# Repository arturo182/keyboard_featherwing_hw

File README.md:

# The Keyboard FeatherWing

The Keyboard FeatherWing is an easy way to add a handheld Qwerty keyboard and a 2.6 color display (+ more) to your project! It fits well in your hands and is great for typing with your thumbs, early 2000s-style.

The FeatherWing itself does not contain an MCU/CPU/SoC that you can program; you will need a board compatible with the [Adafruit Feather System](https://learn.adafruit.com/adafruit-feather/feather-specification).

# Technical details
- 2.6 320x240 16-bit color LCD with resistive touch screen
- QWERTY keyboard
- 5-way button
- 4 soft tactile buttons
- A Neopixel
- microSD connector
- Stemma QT/Qwiic connector
- On/Off switch
- Dual row sockets
- Four mounting holes
- GPIO solder jumpers

# Links

For more information visit https://kfw.solder.party/

You can find example code here: https://github.com/arturo182/keyboard_featherwing_sw

This board uses a ATSAMD20 chip as a i2c peripheral that can be polled to get the key FIFO, the firmware for the SAM can be found here: https://github.com/arturo182/bbq10kbd_i2c_sw

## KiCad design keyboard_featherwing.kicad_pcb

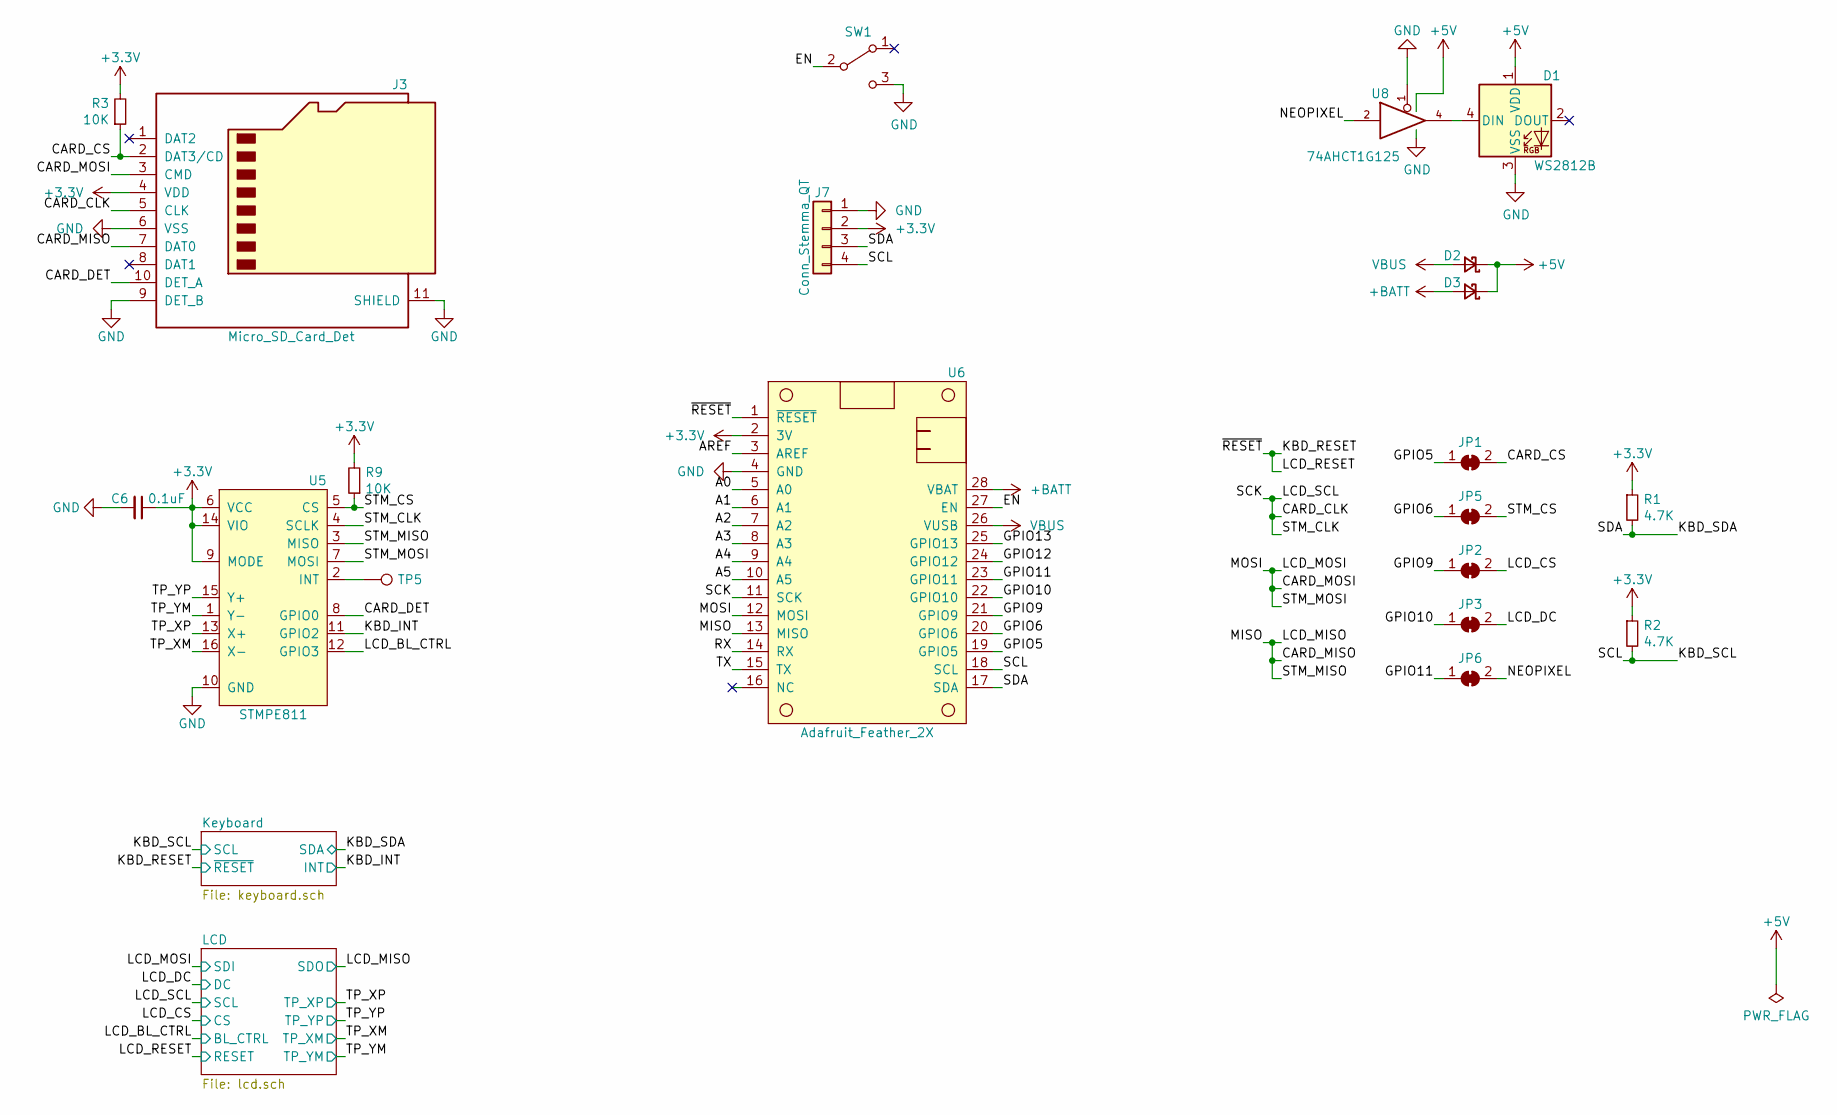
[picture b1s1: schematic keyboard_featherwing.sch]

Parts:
C6: 0.1uF; C_0603_1608Metric
D1: WS2812B; LED_WS2812B_PLCC4_5.0x5.0mm_P3.2mm
D2, D3: S1JHE; D_SOD-323_HandSoldering
J3: Micro_SD_Card_Det; microSD_HC_Molex_104031-0811
J7: Conn_Stemma_QT; JST_SH_SM04B-SRSS-TB_1x04-1MP_P1.00mm_Horizontal
JP1: SB_CARD_CS; SolderJumper-2_P1.3mm_Bridged_RoundedPad1.0x1.5mm
JP2: SB_LCD_CS; SolderJumper-2_P1.3mm_Bridged_RoundedPad1.0x1.5mm
JP3: SB_LCD_DC; SolderJumper-2_P1.3mm_Bridged_RoundedPad1.0x1.5mm
JP5: SB_STM_CS; SolderJumper-2_P1.3mm_Bridged_RoundedPad1.0x1.5mm
JP6: SB_NEOPIXEL; SolderJumper-2_P1.3mm_Bridged_RoundedPad1.0x1.5mm
R1, R2: 4.7K; R_0603_1608Metric
R3, R9: 10K; R_0603_1608Metric
SW1: SW_EN; SW_SPDT_PCM12
TP5: TP_STM_INT; TestPoint_Pad_D3.0mm
U5: STMPE811; QFN-16-1EP_3x3mm_P0.5mm_EP1.75x1.75mm
U6: Adafruit_Feather_2X; FeatherWing
U8: 74AHCT1G125; SOT-353_SC-70-5

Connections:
+3V3: C6.1, J3.4 (VDD), J7.2, R1.1, R2.1, R3.2, R9.2, U5.6 (VCC), U5.9 (MODE), U5.14 (VIO), U6.2 (3V); also elsewhere on the board
+5V: D1.1 (VDD), D2.1 (K), D3.1 (K), U8.5 (VCC)
+BATT: D3.2 (A), U6.28 (VBAT)
/A0: U6.5 (A0)
/A1: U6.6 (A1)
/A2: U6.7 (A2)
/A3: U6.8 (A3)
/A4: U6.9 (A4)
/A5: U6.10 (A5)
/AREF: U6.3 (AREF)
/CARD_CLK: J3.5 (CLK), U5.4 (SCLK), U6.11 (SCK); also elsewhere on the board
/CARD_CS: J3.2 (DAT3/CD), JP1.2 (B), R3.1
/CARD_DET: J3.10 (DET_A), U5.8 (GPIO0)
/CARD_MISO: J3.7 (DAT0), U5.3 (MISO), U6.13 (MISO); also elsewhere on the board
/CARD_MOSI: J3.3 (CMD), U5.7 (MOSI), U6.12 (MOSI); also elsewhere on the board
/EN: SW1.2 (B), U6.27 (EN)
/GPIO5: JP1.1 (A), U6.19 (GPIO5)
/GPIO6: JP5.1 (A), U6.20 (GPIO6)
/GPIO9: JP2.1 (A), U6.21 (GPIO9)
/GPIO10: JP3.1 (A), U6.22 (GPIO10)
/GPIO11: JP6.1 (A), U6.23 (GPIO11)
/GPIO12: U6.24 (GPIO12)
/GPIO13: U6.25 (GPIO13)
/KBD_INT: U5.11 (GPIO2); also elsewhere on the board
/KBD_RESET: U6.1 (~RESET~); also elsewhere on the board
/KBD_SCL: J7.4, R2.2, U6.18 (SCL); also elsewhere on the board
/KBD_SDA: J7.3, R1.2, U6.17 (SDA); also elsewhere on the board
/LCD_BL_CTRL: U5.12 (GPIO3); also elsewhere on the board
/LCD_CS: JP2.2 (B); also elsewhere on the board
/LCD_DC: JP3.2 (B); also elsewhere on the board
/NEOPIXEL: JP6.2 (B), U8.2
/RX: U6.14 (RX)
/STM_CS: JP5.2 (B), R9.1, U5.5 (CS)
/TP_XM: U5.16 (X-); also elsewhere on the board
/TP_XP: U5.13 (X+); also elsewhere on the board
/TP_YM: U5.1 (Y-); also elsewhere on the board
/TP_YP: U5.15 (Y+); also elsewhere on the board
/TX: U6.15 (TX)
GND: C6.2, D1.3 (VSS), J3.6 (VSS), J3.9 (DET_B), J3.11 (SHIELD), J7.1, SW1.3 (C), U5.10 (GND), U6.4 (GND), U8.1, U8.3 (GND); also elsewhere on the board
unnamed: D1.4 (DIN), U8.4
unnamed: TP5.1, U5.2 (INT)
VBUS: D2.2 (A), U6.26 (VUSB)

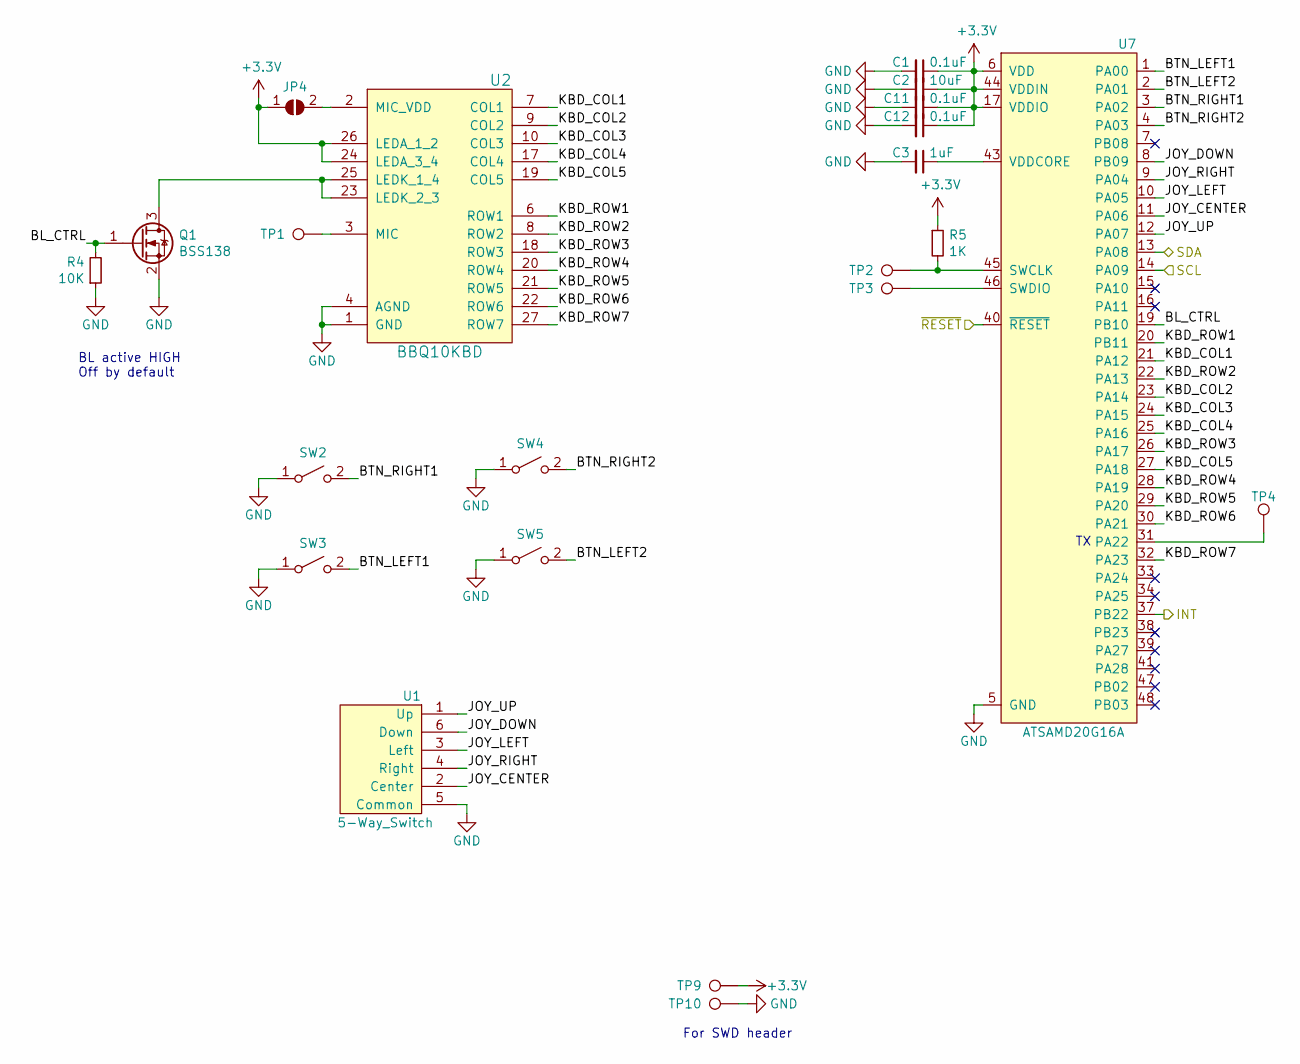
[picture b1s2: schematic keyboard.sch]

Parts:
C1, C11, C12: 0.1uF; C_0603_1608Metric
C2: 10uF; C_0603_1608Metric
C3: 1uF; C_0603_1608Metric
JP4: SB_MIC_VDD; SolderJumper-2_P1.3mm_Open_RoundedPad1.0x1.5mm
Q1: BSS138; SOT-23
R4: 10K; R_0603_1608Metric
R5: 1K; R_0603_1608Metric
SW2: SW_RIGHT1; RMT-CZ66
SW3: SW_LEFT1; RMT-CZ66
SW4: SW_RIGHT2; RMT-CZ66
SW5: SW_LEFT2; RMT-CZ66
TP1: TP_MIC; TestPoint_Pad_D3.0mm
TP2: TP_KBD_SWCLK; TestPoint_Pad_D3.0mm
TP3: TP_KBD_SWDIO; TestPoint_Pad_D3.0mm
TP4: TP_KBD_TX; TestPoint_Pad_D3.0mm
TP9: TP_KBD_3V; TestPoint_Pad_D3.0mm
TP10: TP_KBD_GND; TestPoint_Pad_D3.0mm
U1: 5-Way_Switch; SF303GJ26
U2: BBQ10KBD; BM14B(0.8)-24DS-0.4V(53)
U7: ATSAMD20G16A; QFN-48-1EP_7x7mm_P0.5mm_EP5.15x5.15mm

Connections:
+3V3: C1.1, C2.1, C11.1, C12.1, JP4.1 (A), R5.1, TP9.1, U2.24 (LEDA_3_4), U2.26 (LEDA_1_2), U7.6 (VDD), U7.17 (VDDIO), U7.36 (VDDIO), U7.44 (VDDIN); also elsewhere on the board
/KBD_INT: U7.37 (PB22); also elsewhere on the board
/KBD_RESET: U7.40 (~RESET~); also elsewhere on the board
/KBD_SCL: U7.14 (PA09); also elsewhere on the board
/KBD_SDA: U7.13 (PA08); also elsewhere on the board
/Keyboard/BL_CTRL: Q1.1 (G), R4.2, U7.19 (PB10)
/Keyboard/BTN_LEFT1: SW3.2 (B), U7.1 (PA00)
/Keyboard/BTN_LEFT2: SW5.2 (B), U7.2 (PA01)
/Keyboard/BTN_RIGHT1: SW2.2 (B), U7.3 (PA02)
/Keyboard/BTN_RIGHT2: SW4.2 (B), U7.4 (PA03)
/Keyboard/JOY_CENTER: U1.2 (Center), U7.11 (PA06)
/Keyboard/JOY_DOWN: U1.6 (Down), U7.8 (PB09)
/Keyboard/JOY_LEFT: U1.3 (Left), U7.10 (PA05)
/Keyboard/JOY_RIGHT: U1.4 (Right), U7.9 (PA04)
/Keyboard/JOY_UP: U1.1 (Up), U7.12 (PA07)
/Keyboard/KBD_COL1: U2.7 (COL1), U7.21 (PA12)
/Keyboard/KBD_COL2: U2.9 (COL2), U7.23 (PA14)
/Keyboard/KBD_COL3: U2.10 (COL3), U7.24 (PA15)
/Keyboard/KBD_COL4: U2.17 (COL4), U7.25 (PA16)
/Keyboard/KBD_COL5: U2.19 (COL5), U7.27 (PA18)
/Keyboard/KBD_ROW1: U2.6 (ROW1), U7.20 (PB11)
/Keyboard/KBD_ROW2: U2.8 (ROW2), U7.22 (PA13)
/Keyboard/KBD_ROW3: U2.18 (ROW3), U7.26 (PA17)
/Keyboard/KBD_ROW4: U2.20 (ROW4), U7.28 (PA19)
/Keyboard/KBD_ROW5: U2.21 (ROW5), U7.29 (PA20)
/Keyboard/KBD_ROW6: U2.22 (ROW6), U7.30 (PA21)
/Keyboard/KBD_ROW7: U2.27 (ROW7), U7.32 (PA23)
GND: C1.2, C2.2, C3.2, C11.2, C12.2, Q1.2 (S), R4.1, SW2.1 (A), SW3.1 (A), SW4.1 (A), SW5.1 (A), TP10.1, U1.5 (Common), U1.SHIELD, U2.1 (GND), U2.4 (AGND), U2.5 (GND), U2.11 (GND), U2.12 (GND), U2.13 (GND), U2.14 (GND), U2.15 (GND), U2.16 (GND), U2.28 (GND), U7.5 (GND), U7.18 (GND), U7.35 (GND), U7.42 (GND); also elsewhere on the board
unnamed: C3.1, U7.43 (VDDCORE)
unnamed: JP4.2 (B), U2.2 (MIC_VDD)
unnamed: Q1.3 (D), U2.23 (LEDK_2_3), U2.25 (LEDK_1_4)
unnamed: R5.2, TP2.1, U7.45 (SWCLK)
unnamed: TP1.1, U2.3 (MIC)
unnamed: TP3.1, U7.46 (SWDIO)
unnamed: TP4.1, U7.31 (PA22)

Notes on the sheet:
BL active HIGH Off by default
For SWD header

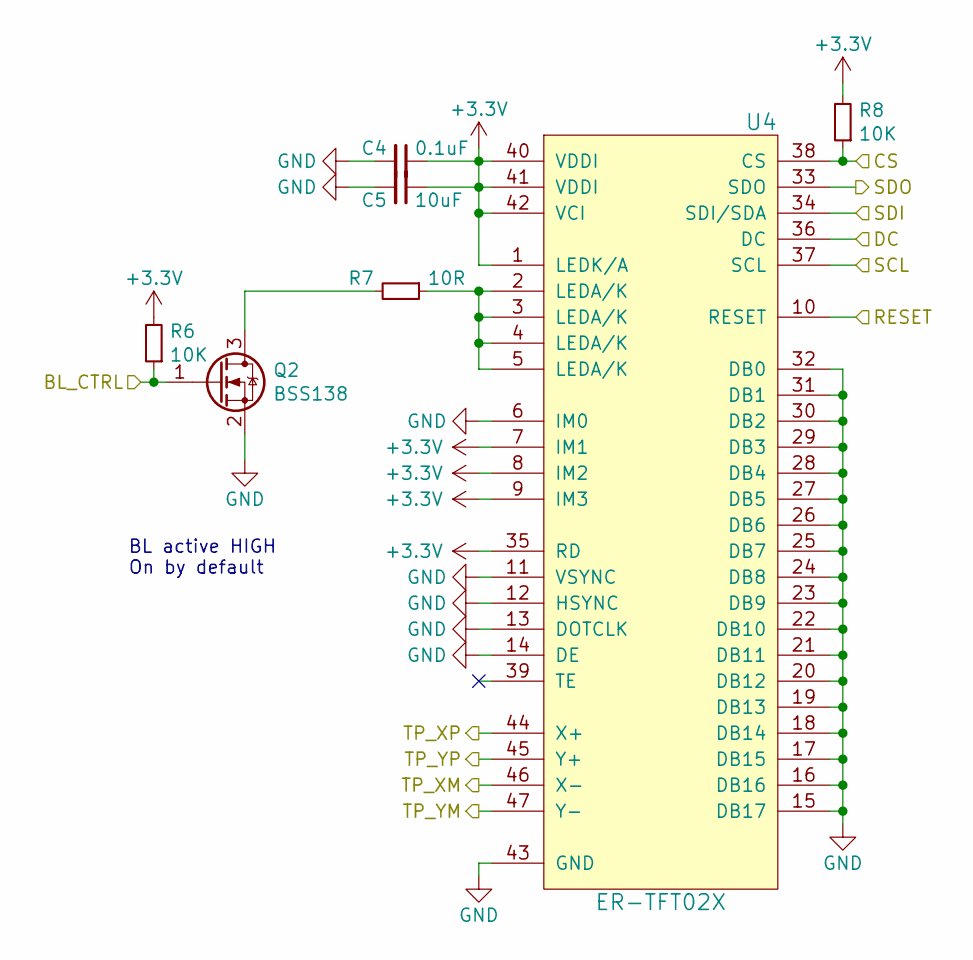
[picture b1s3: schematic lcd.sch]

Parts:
C4: 0.1uF; C_0603_1608Metric
C5: 10uF; C_0603_1608Metric
Q2: BSS138; SOT-23
R6, R8: 10K; R_0603_1608Metric
R7: 10R; R_0603_1608Metric
U4: ER-TFT02X; ER-CON50HT-1

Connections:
+3V3: C4.1, C5.1, R6.2, R8.2, U4.1 (LEDK/A), U4.7 (IM1), U4.8 (IM2), U4.9 (IM3), U4.35 (RD), U4.40 (VDDI), U4.41 (VDDI), U4.42 (VCI); also elsewhere on the board
/CARD_CLK: U4.37 (SCL); also elsewhere on the board
/CARD_MISO: U4.33 (SDO); also elsewhere on the board
/CARD_MOSI: U4.34 (SDI/SDA); also elsewhere on the board
/KBD_RESET: U4.10 (RESET); also elsewhere on the board
/LCD_BL_CTRL: Q2.1 (G), R6.1; also elsewhere on the board
/LCD_CS: R8.1, U4.38 (CS); also elsewhere on the board
/LCD_DC: U4.36 (DC); also elsewhere on the board
/TP_XM: U4.46 (X-); also elsewhere on the board
/TP_XP: U4.44 (X+); also elsewhere on the board
/TP_YM: U4.47 (Y-); also elsewhere on the board
/TP_YP: U4.45 (Y+); also elsewhere on the board
GND: C4.2, C5.2, Q2.2 (S), U4.6 (IM0), U4.11 (VSYNC), U4.12 (HSYNC), U4.13 (DOTCLK), U4.14 (DE), U4.15 (DB17), U4.16 (DB16), U4.17 (DB15), U4.18 (DB14), U4.19 (DB13), U4.20 (DB12), U4.21 (DB11), U4.22 (DB10), U4.23 (DB9), U4.24 (DB8), U4.25 (DB7), U4.26 (DB6), U4.27 (DB5), U4.28 (DB4), U4.29 (DB3), U4.30 (DB2), U4.31 (DB1), U4.32 (DB0), U4.43 (GND), U4.48 (GND), U4.49 (GND), U4.50 (GND); also elsewhere on the board
unnamed: Q2.3 (D), R7.2
unnamed: R7.1, U4.2 (LEDA/K), U4.3 (LEDA/K), U4.4 (LEDA/K), U4.5 (LEDA/K)

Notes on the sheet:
BL active HIGH On by default

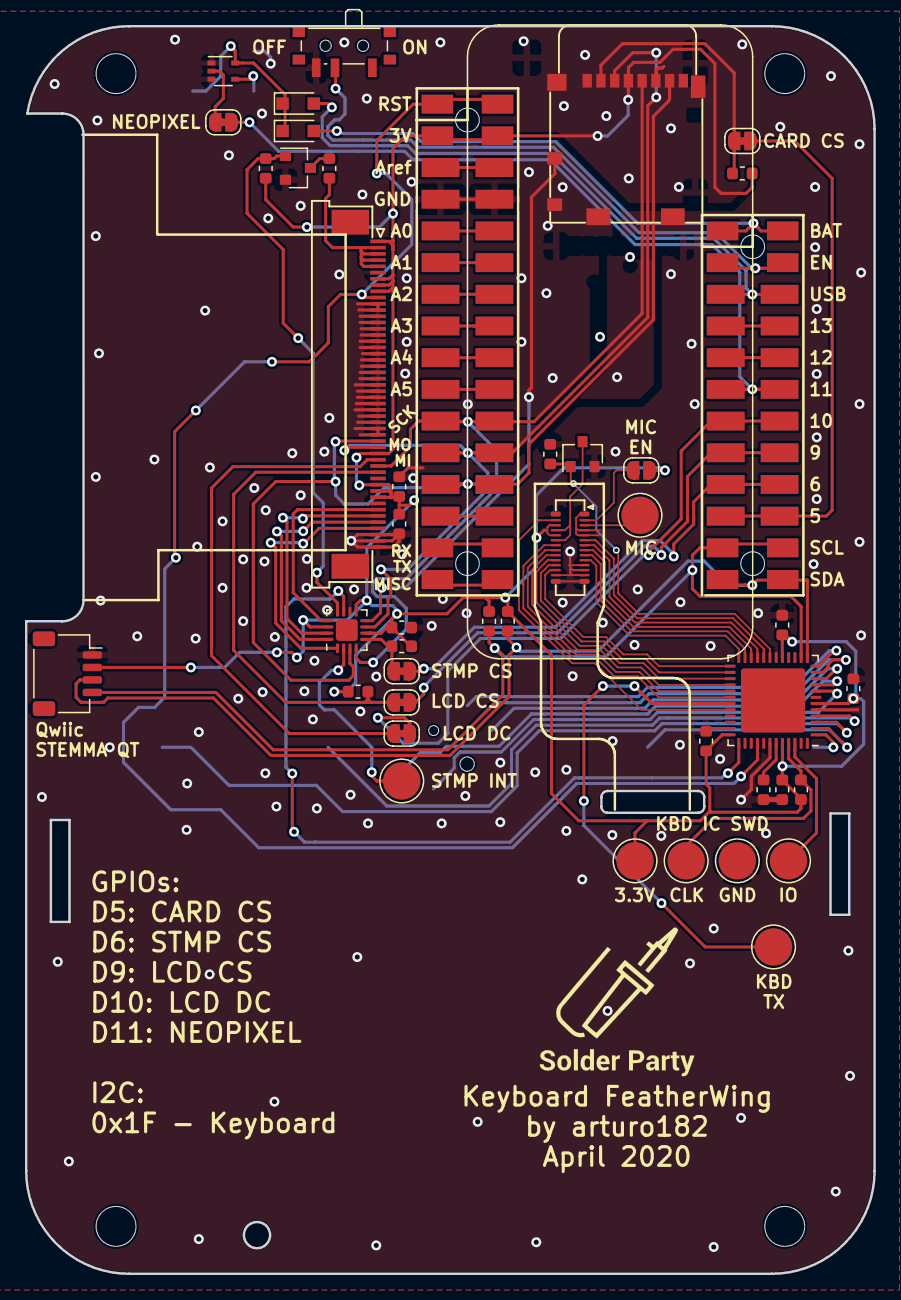
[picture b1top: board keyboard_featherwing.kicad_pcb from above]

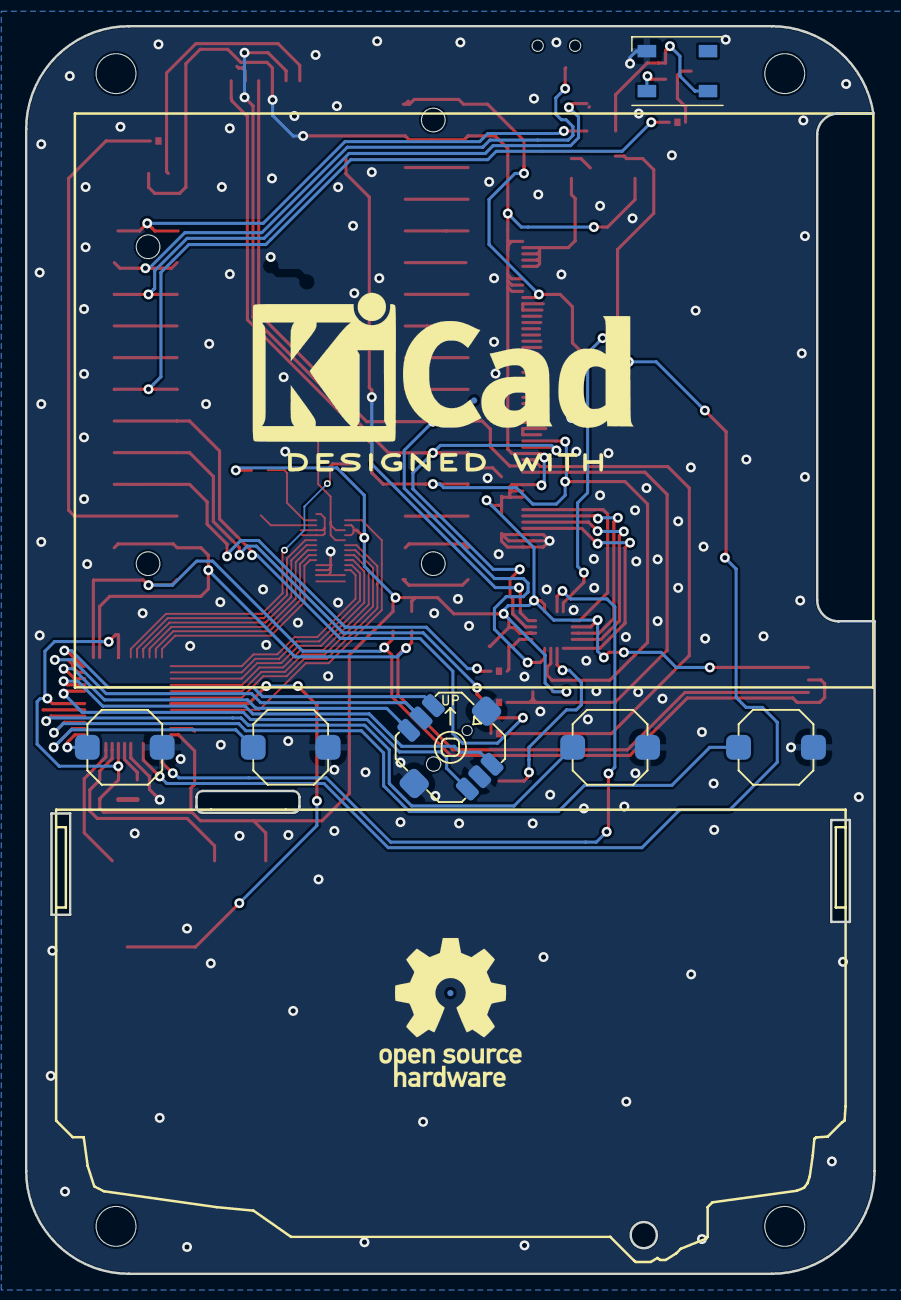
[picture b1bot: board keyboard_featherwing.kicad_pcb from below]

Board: 2 copper layers, 68.0 x 100.0 mm, 49 parts (6 on the bottom side), 62 nets.

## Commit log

2019-05-08 Initial import
2019-06-15 Finish up rev1
2019-07-05 rev2
2020-03-24 Rev 3
2020-04-09 Rev 4!
2020-08-16 Rename handheld->keyboard
2020-08-16 Rev5, production
2020-08-16 Add license and README
2020-08-19 Update .step to rev5
